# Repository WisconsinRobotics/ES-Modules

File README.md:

# ES-Modules
Daughter board code and CAD files for the 2018 rover

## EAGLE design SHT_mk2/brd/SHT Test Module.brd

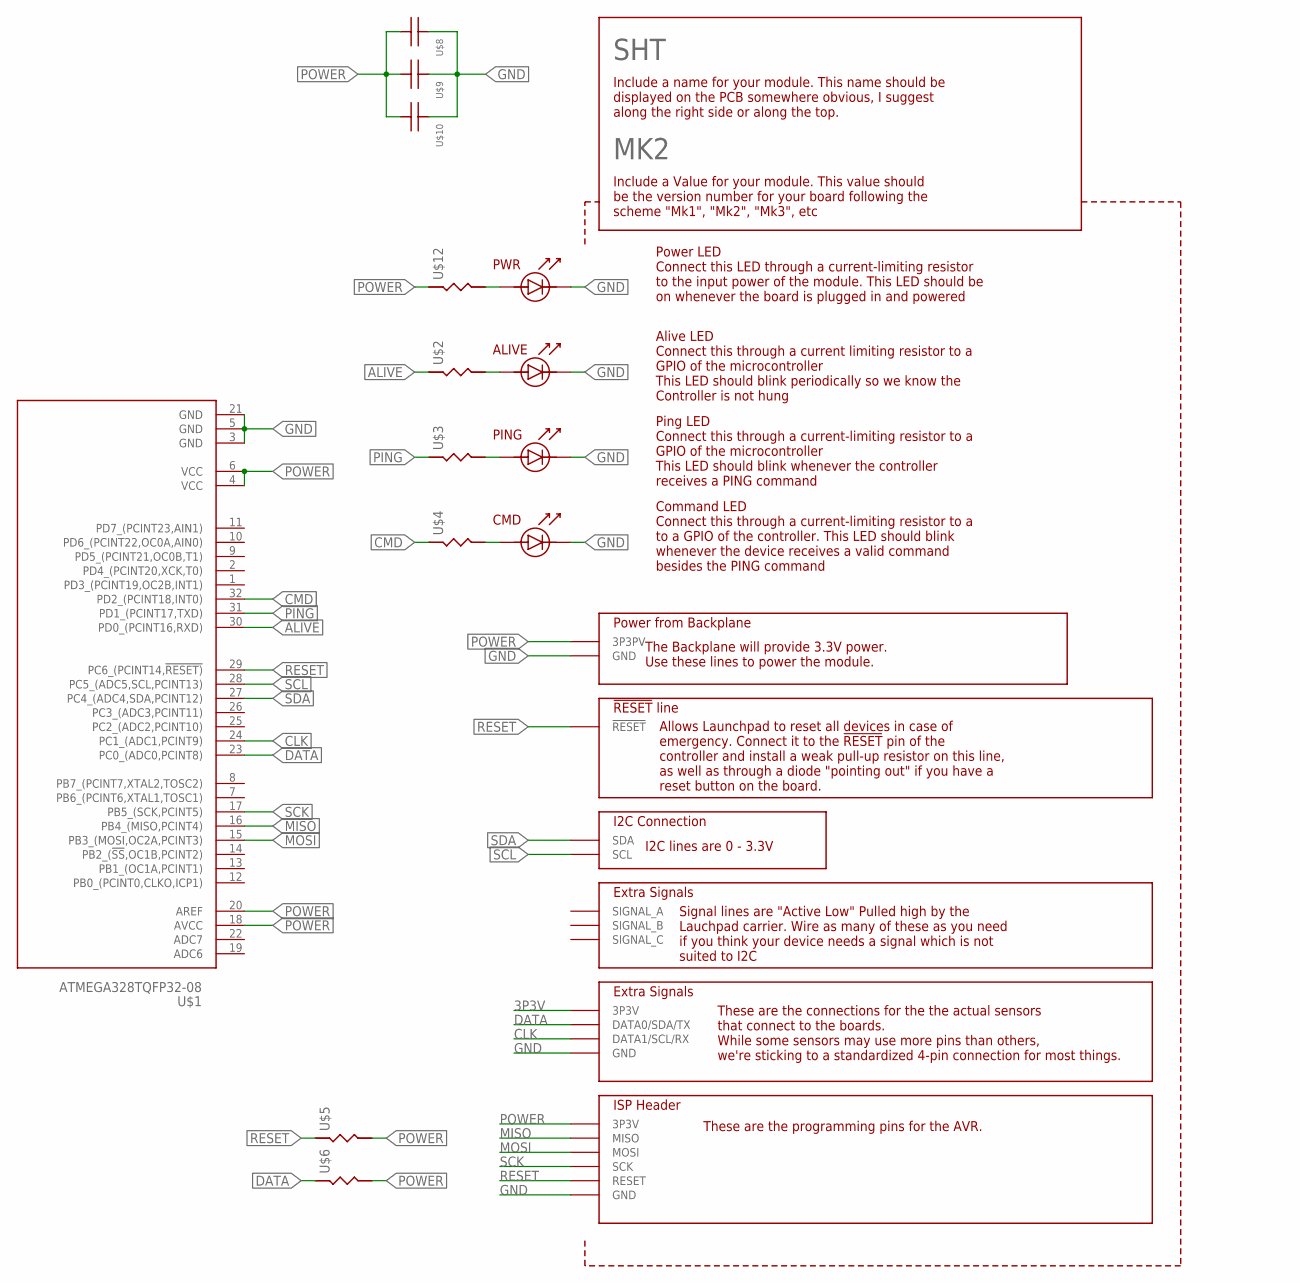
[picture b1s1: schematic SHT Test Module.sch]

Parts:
SHT: MK2; SENSOR_MODULE_MK1
U$1: ATMEGA328TQFP32-08; TQFP32-08
U$2, U$3, U$4, U$5, U$6, U$12: RESISTOR; 0805_STACKPOLERESISTOR
U$8, U$9, U$10: CAPACITOR-UNPOLARIZED0805; 0805_STACKPOLERESISTOR

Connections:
3P3V: SHT.3P3V@2 (3P3V), SHT.3P3V@3 (3P3V)
ALIVE: U$1.30 (PD0_(PCINT16,RXD)), U$2.P$1
CLK: SHT.DATA1@1 (DATA1/SCL/RX), SHT.DATA1@2 (DATA1/SCL/RX), U$1.24 (PC1_(ADC1,PCINT9))
CMD: U$1.32 (PD2_(PCINT18,INT0)), U$4.P$1
DATA: SHT.DATA0@1 (DATA0/SDA/TX), SHT.DATA0@2 (DATA0/SDA/TX), U$1.23 (PC0_(ADC0,PCINT8)), U$6.P$1
GND: SHT.ALIVELED_CATHODE, SHT.CMDLED_CATHODE, SHT.GND@1 (GND), SHT.GND@2 (GND), SHT.GND@3 (GND), SHT.GND@4 (GND), SHT.PINGLED_CATHODE, SHT.PWRLED_CATHODE, U$1.3 (GND), U$1.5 (GND), U$1.21 (GND), U$8.P$1, U$9.P$1, U$10.P$1
MISO: SHT.MISO, U$1.16 (PB4_(MISO,PCINT4))
MOSI: SHT.MOSI, U$1.15 (PB3_(MOSI,OC2A,PCINT3))
unnamed: SHT.PWRLED_ANODE, U$12.P$2
unnamed: SHT.ALIVELED_ANODE, U$2.P$2
unnamed: SHT.PINGLED_ANODE, U$3.P$2
unnamed: SHT.CMDLED_ANODE, U$4.P$2
PING: U$1.31 (PD1_(PCINT17,TXD)), U$3.P$1
POWER: SHT.3P3V@1 (3P3PV), SHT.3P3V@4 (3P3V), U$1.4 (VCC), U$1.6 (VCC), U$1.18 (AVCC), U$1.20 (AREF), U$5.P$2, U$6.P$2, U$8.P$2, U$9.P$2, U$10.P$2, U$12.P$1
RESET: SHT.RESET@1 (!RESET), SHT.RESET@2 (RESET), U$1.29 (PC6_(PCINT14,!RESET)), U$5.P$1
SCK: SHT.SCK, U$1.17 (PB5_(SCK,PCINT5))
SCL: SHT.SCL, U$1.28 (PC5_(ADC5,SCL,PCINT13))
SDA: SHT.SDA, U$1.27 (PC4_(ADC4,SDA,PCINT12))

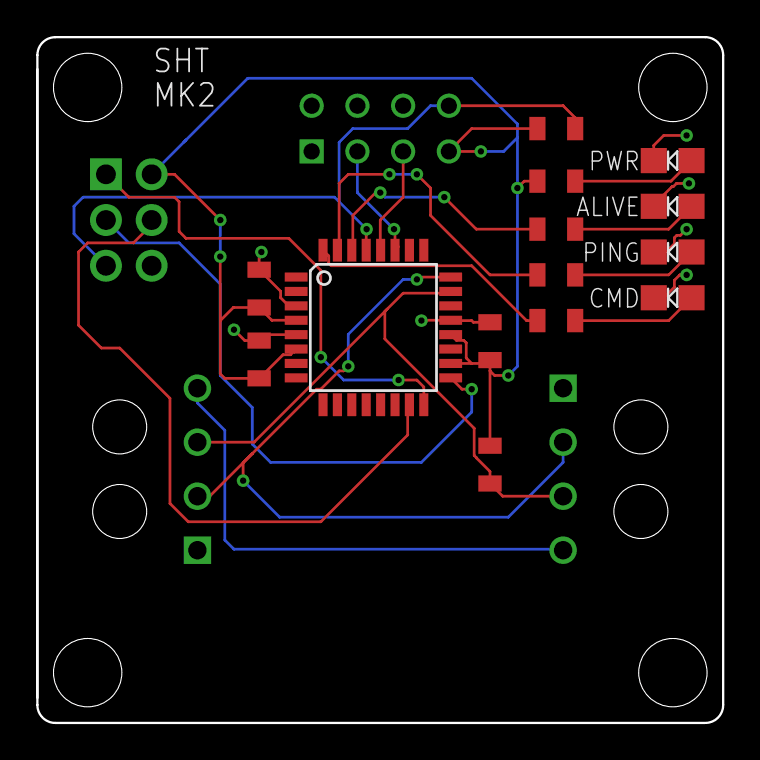
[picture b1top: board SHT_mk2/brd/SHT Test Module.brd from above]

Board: 2 copper layers, 38.1 x 38.1 mm, 11 parts (0 on the bottom side), 18 nets.

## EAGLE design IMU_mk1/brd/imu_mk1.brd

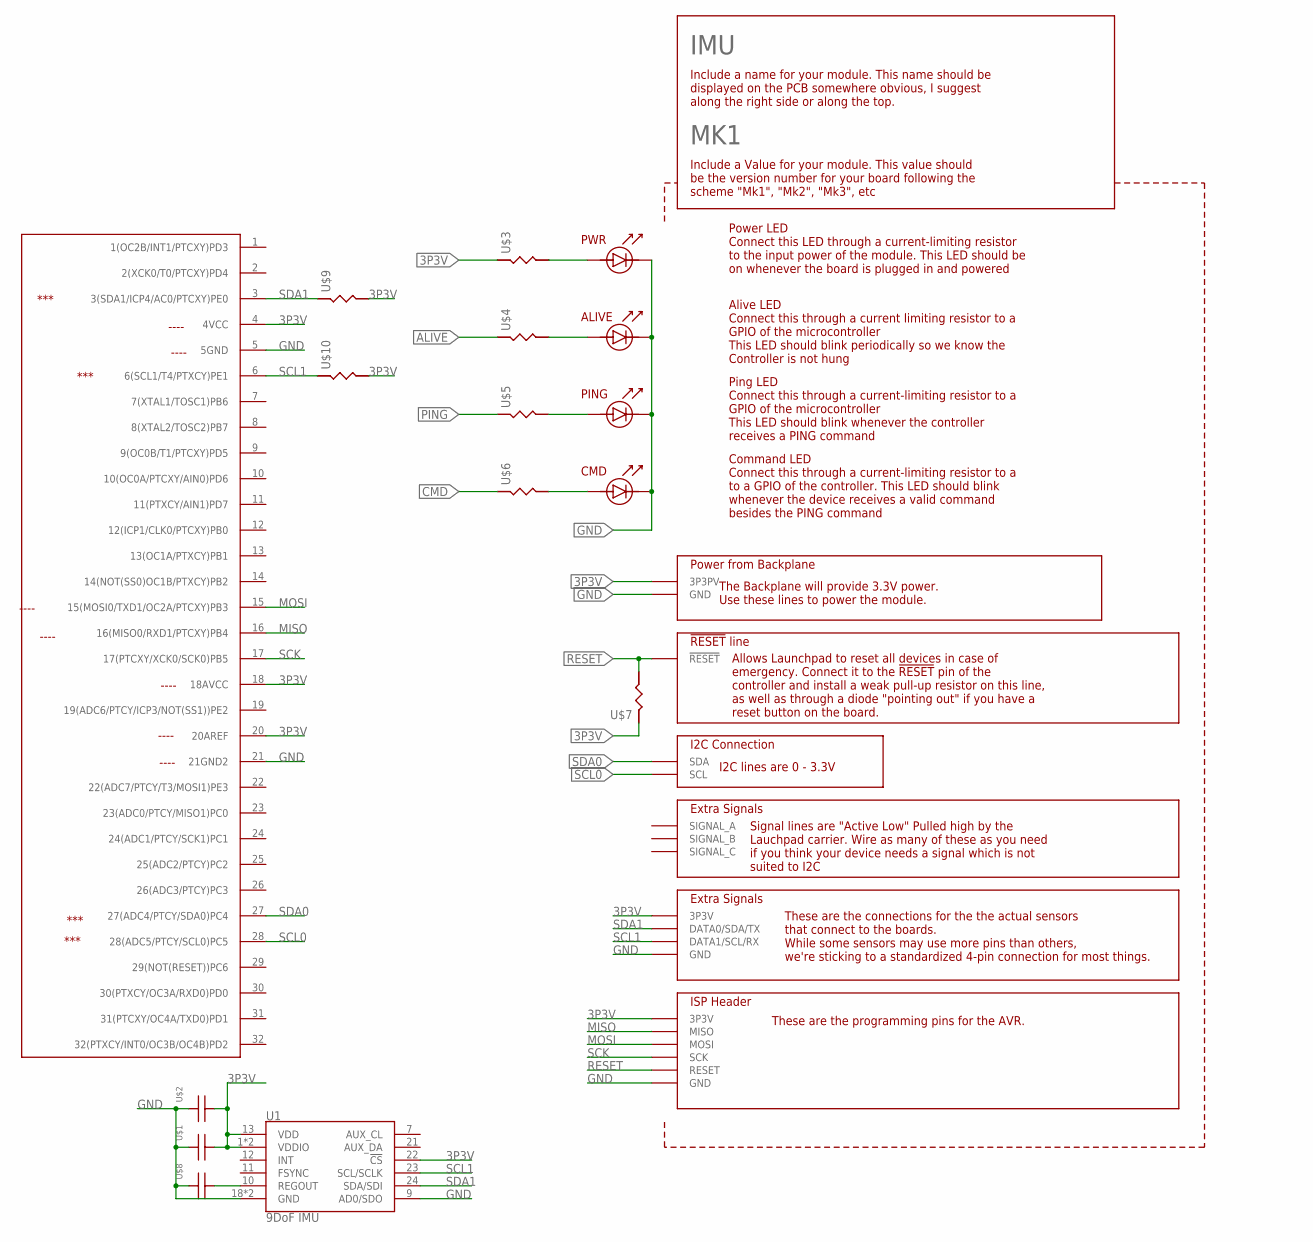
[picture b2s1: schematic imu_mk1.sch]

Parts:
IMU: MK1; SENSOR_MODULE_MK1
U1: 9DoF IMU; QFN24-3X3
U100: ATMEGA328PB; TQFP32-08
U$1, U$2, U$8: CAPACITOR-UNPOLARIZED0805; 0805_STACKPOLERESISTOR
U$3, U$4, U$5, U$6, U$7, U$9, U$10: RESISTOR; 0805_STACKPOLERESISTOR

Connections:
3P3V: IMU.3P3V@1 (3P3PV), IMU.3P3V@2 (3P3V), IMU.3P3V@3 (3P3V), IMU.3P3V@4 (3P3V), U1.1 (VDDIO), U1.8 (VDDIO), U1.13 (VDD), U1.22 (!CS), U100.4 (4VCC), U100.18 (18AVCC), U100.20 (20AREF), U$1.P$2, U$2.P$2, U$3.P$1, U$7.P$1, U$9.P$2, U$10.P$2
ALIVE: U$4.P$1
CMD: U$6.P$1
GND: IMU.ALIVELED_CATHODE, IMU.CMDLED_CATHODE, IMU.GND@1 (GND), IMU.GND@2 (GND), IMU.GND@3 (GND), IMU.GND@4 (GND), IMU.PINGLED_CATHODE, IMU.PWRLED_CATHODE, U1.9 (AD0/SDO), U1.18 (GND), U1.20 (GND), U100.5 (5GND), U100.21 (21GND2), U$1.P$1, U$2.P$1, U$8.P$1
MISO: IMU.MISO, U100.16 (16(MISO0/RXD1/PTCXY)PB4)
MOSI: IMU.MOSI, U100.15 (15(MOSI0/TXD1/OC2A/PTCXY)PB3)
unnamed: IMU.PWRLED_ANODE, U$3.P$2
unnamed: IMU.ALIVELED_ANODE, U$4.P$2
unnamed: IMU.PINGLED_ANODE, U$5.P$2
unnamed: IMU.CMDLED_ANODE, U$6.P$2
PING: U$5.P$1
REGOUT: U1.10 (REGOUT), U$8.P$2
RESET: IMU.RESET@1 (!RESET), IMU.RESET@2 (RESET), U$7.P$2
SCK: IMU.SCK, U100.17 (17(PTCXY/XCK0/SCK0)PB5)
SCL0: IMU.SCL, U100.28 (28(ADC5/PTCY/SCL0)PC5)
SCL1: IMU.DATA1@1 (DATA1/SCL/RX), IMU.DATA1@2 (DATA1/SCL/RX), U1.23 (SCL/SCLK), U100.6 (6(SCL1/T4/PTXCY)PE1), U$10.P$1
SDA0: IMU.SDA, U100.27 (27(ADC4/PTCY/SDA0)PC4)
SDA1: IMU.DATA0@1 (DATA0/SDA/TX), IMU.DATA0@2 (DATA0/SDA/TX), U1.24 (SDA/SDI), U100.3 (3(SDA1/ICP4/AC0/PTCXY)PE0), U$9.P$1

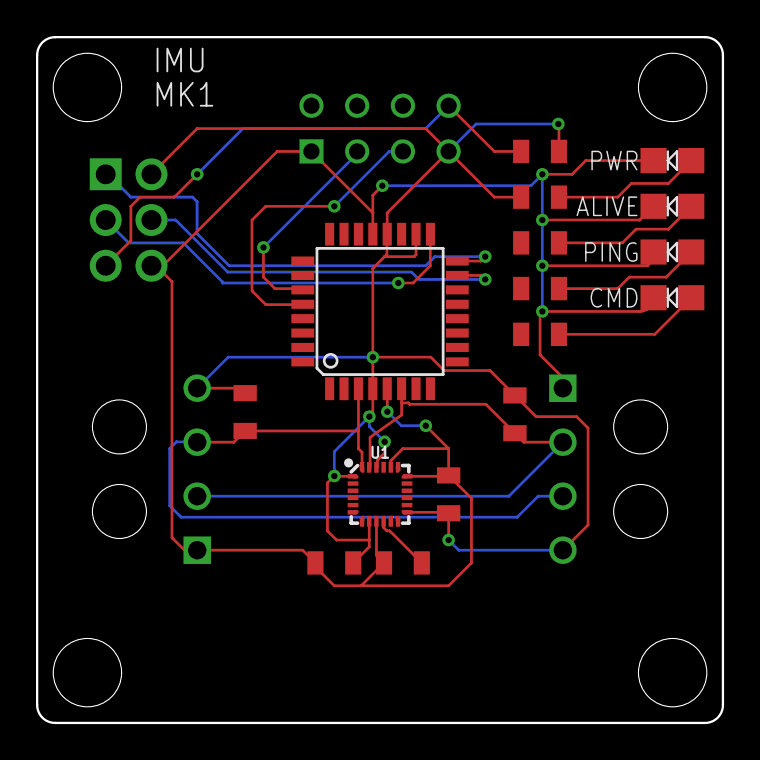
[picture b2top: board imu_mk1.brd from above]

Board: 2 copper layers, 38.1 x 38.1 mm, 13 parts (0 on the bottom side), 15 nets.

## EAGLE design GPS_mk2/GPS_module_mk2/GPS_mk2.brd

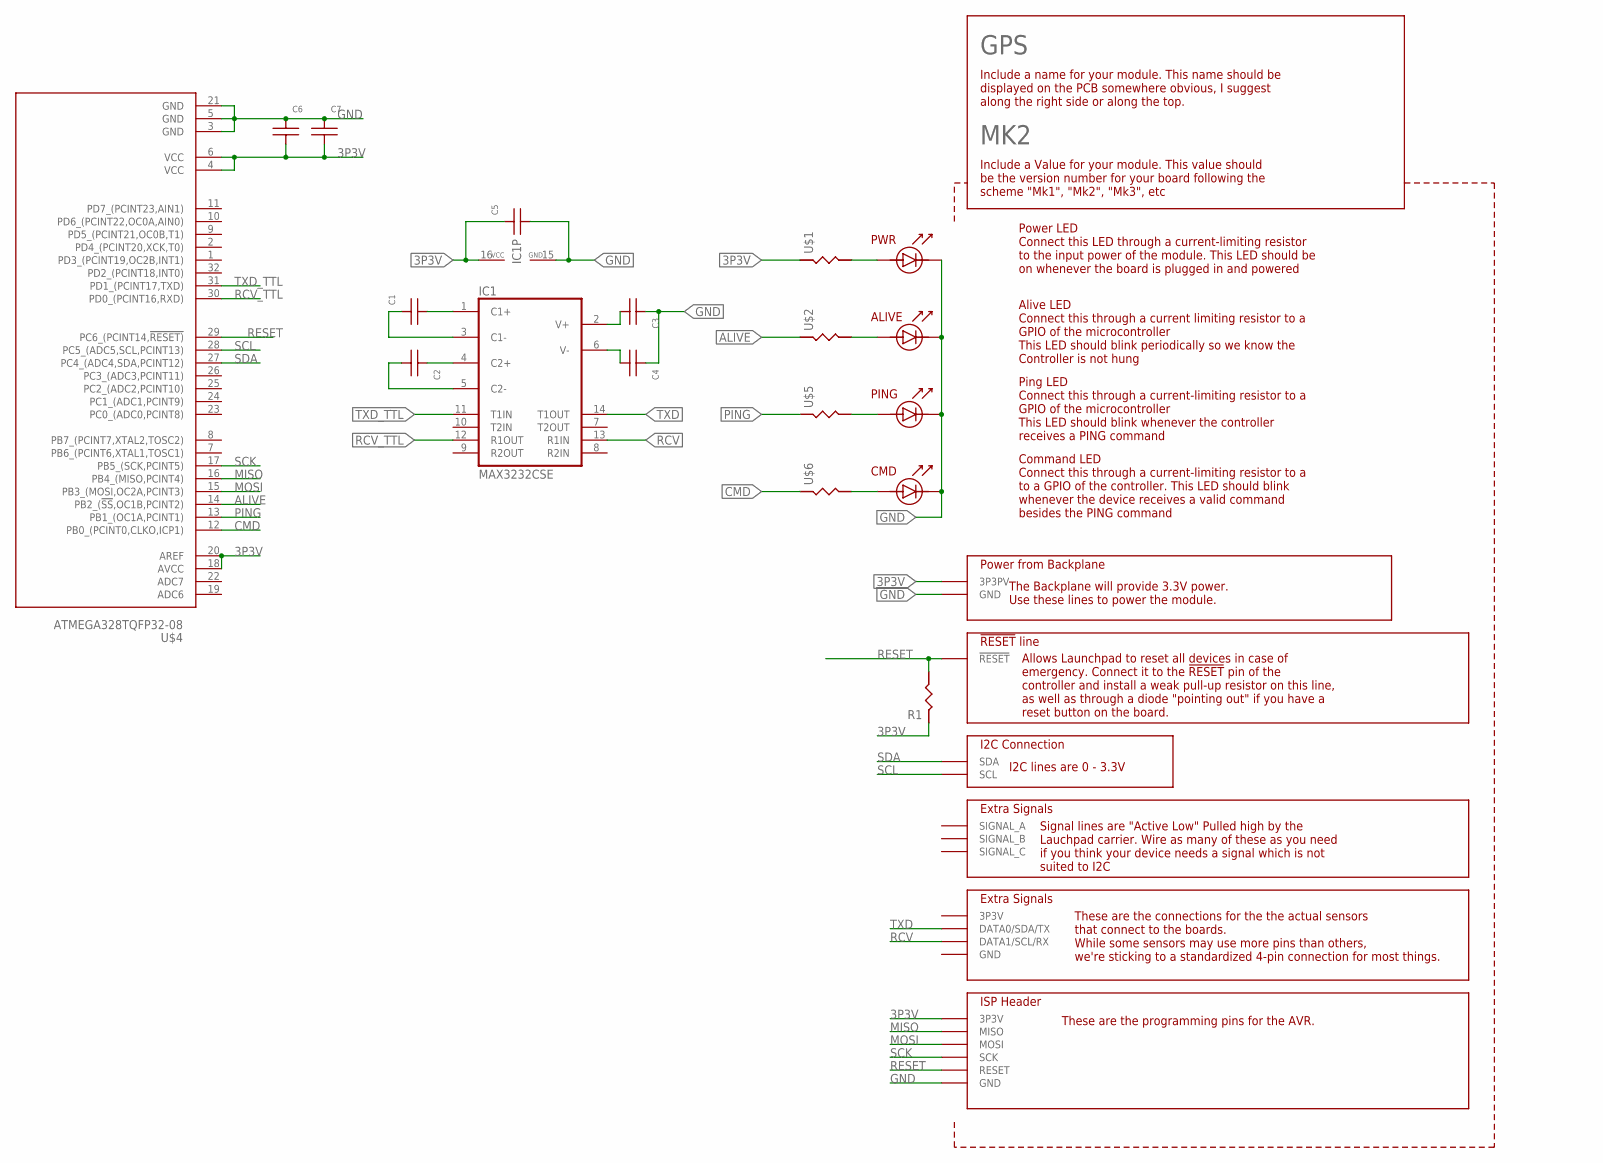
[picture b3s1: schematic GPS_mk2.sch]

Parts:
C1, C2, C3, C4, C5, C6, C7: CAPACITOR-UNPOLARIZED0805; 0805_STACKPOLERESISTOR
GPS: MK2; SENSOR_MODULE_MK1
IC1: MAX3232CSE; SO16
R1: RESISTOR; 0805_STACKPOLERESISTOR
U$1, U$2, U$5, U$6: RESISTOR; 0805_STACKPOLERESISTOR
U$4: ATMEGA328TQFP32-08; TQFP32-08

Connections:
3P3V: C5.P$1, C6.P$2, C7.P$2, GPS.3P3V@1 (3P3PV), GPS.3P3V@4 (3P3V), IC1.16 (VCC), R1.P$1, U$1.P$1, U$4.4 (VCC), U$4.6 (VCC), U$4.18 (AVCC), U$4.20 (AREF)
ALIVE: U$2.P$1, U$4.14 (PB2_(!SS,OC1B,PCINT2))
CMD: U$4.12 (PB0_(PCINT0,CLKO,ICP1)), U$6.P$1
GND: C3.P$1, C4.P$1, C5.P$2, C6.P$1, C7.P$1, GPS.ALIVELED_CATHODE, GPS.CMDLED_CATHODE, GPS.GND@1 (GND), GPS.GND@4 (GND), GPS.PINGLED_CATHODE, GPS.PWRLED_CATHODE, IC1.15 (GND), U$4.3 (GND), U$4.5 (GND), U$4.21 (GND)
MISO: GPS.MISO, U$4.16 (PB4_(MISO,PCINT4))
MOSI: GPS.MOSI, U$4.15 (PB3_(MOSI,OC2A,PCINT3))
unnamed: C1.P$2, IC1.1 (C1+)
unnamed: C2.P$1, IC1.4 (C2+)
unnamed: C1.P$1, IC1.3 (C1-)
unnamed: C2.P$2, IC1.5 (C2-)
unnamed: C4.P$2, IC1.6 (V-)
unnamed: GPS.ALIVELED_ANODE, U$2.P$2
unnamed: GPS.PWRLED_ANODE, U$1.P$2
unnamed: GPS.PINGLED_ANODE, U$5.P$2
unnamed: GPS.CMDLED_ANODE, U$6.P$2
unnamed: C3.P$2, IC1.2 (V+)
PING: U$4.13 (PB1_(OC1A,PCINT1)), U$5.P$1
RCV: GPS.DATA1@1 (DATA1/SCL/RX), GPS.DATA1@2 (DATA1/SCL/RX), IC1.13 (R1IN)
RCV_TTL: IC1.12 (R1OUT), U$4.30 (PD0_(PCINT16,RXD))
RESET: GPS.RESET@1 (!RESET), GPS.RESET@2 (RESET), R1.P$2, U$4.29 (PC6_(PCINT14,!RESET))
SCK: GPS.SCK, U$4.17 (PB5_(SCK,PCINT5))
SCL: GPS.SCL, U$4.28 (PC5_(ADC5,SCL,PCINT13))
SDA: GPS.SDA, U$4.27 (PC4_(ADC4,SDA,PCINT12))
TXD: GPS.DATA0@1 (DATA0/SDA/TX), GPS.DATA0@2 (DATA0/SDA/TX), IC1.14 (T1OUT)
TXD_TTL: IC1.11 (T1IN), U$4.31 (PD1_(PCINT17,TXD))

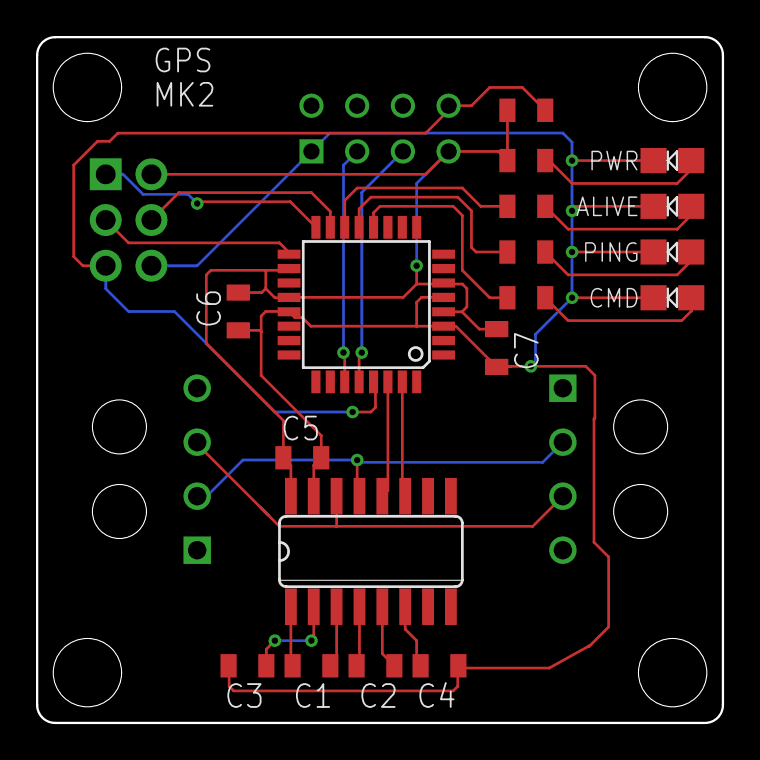
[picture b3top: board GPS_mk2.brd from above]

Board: 2 copper layers, 38.1 x 38.1 mm, 15 parts (0 on the bottom side), 25 nets.

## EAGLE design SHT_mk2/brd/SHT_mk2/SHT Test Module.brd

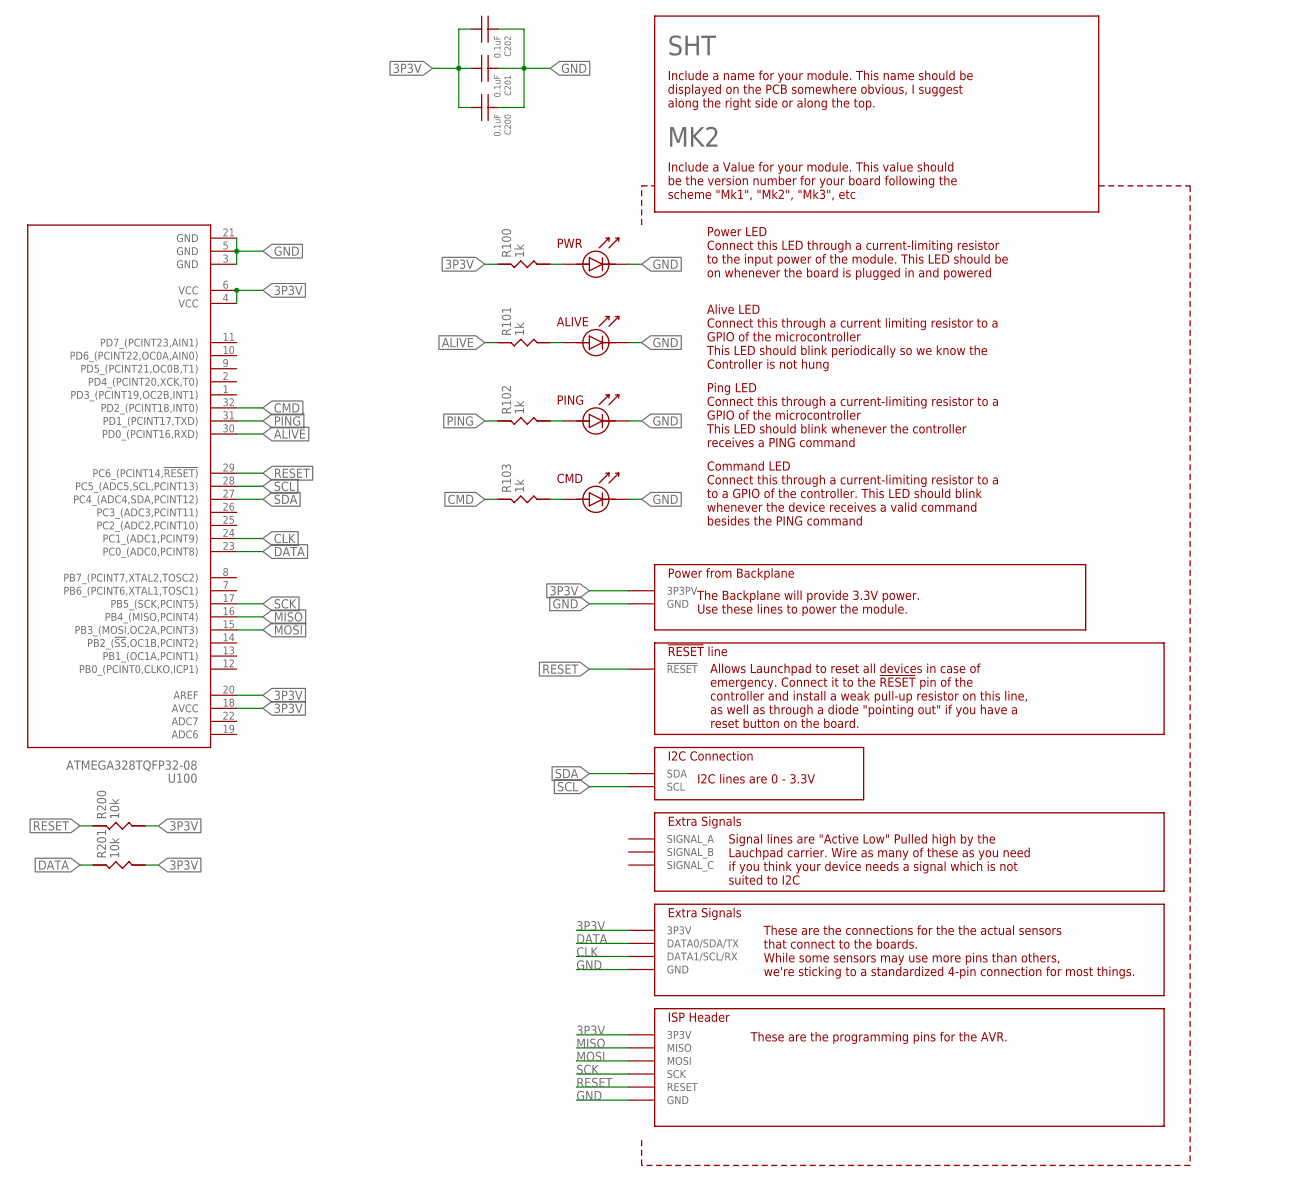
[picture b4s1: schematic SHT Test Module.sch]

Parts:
C200, C201, C202: 0.1uF; 0805_STACKPOLERESISTOR
R100, R101, R102, R103: 1k; 0805_STACKPOLERESISTOR
R200, R201: 10k; 0805_STACKPOLERESISTOR
SHT: MK2; SENSOR_MODULE_MK1
U100: ATMEGA328TQFP32-08; TQFP32-08

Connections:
3P3V: C200.P$2, C201.P$2, C202.P$2, R100.P$1, R200.P$2, R201.P$2, SHT.3P3V@1 (3P3PV), SHT.3P3V@2 (3P3V), SHT.3P3V@3 (3P3V), SHT.3P3V@4 (3P3V), U100.4 (VCC), U100.6 (VCC), U100.18 (AVCC), U100.20 (AREF)
ALIVE: R101.P$1, U100.30 (PD0_(PCINT16,RXD))
CLK: SHT.DATA1@1 (DATA1/SCL/RX), SHT.DATA1@2 (DATA1/SCL/RX), U100.24 (PC1_(ADC1,PCINT9))
CMD: R103.P$1, U100.32 (PD2_(PCINT18,INT0))
DATA: R201.P$1, SHT.DATA0@1 (DATA0/SDA/TX), SHT.DATA0@2 (DATA0/SDA/TX), U100.23 (PC0_(ADC0,PCINT8))
GND: C200.P$1, C201.P$1, C202.P$1, SHT.ALIVELED_CATHODE, SHT.CMDLED_CATHODE, SHT.GND@1 (GND), SHT.GND@2 (GND), SHT.GND@3 (GND), SHT.GND@4 (GND), SHT.PINGLED_CATHODE, SHT.PWRLED_CATHODE, U100.3 (GND), U100.5 (GND), U100.21 (GND)
MISO: SHT.MISO, U100.16 (PB4_(MISO,PCINT4))
MOSI: SHT.MOSI, U100.15 (PB3_(MOSI,OC2A,PCINT3))
unnamed: R100.P$2, SHT.PWRLED_ANODE
unnamed: R101.P$2, SHT.ALIVELED_ANODE
unnamed: R102.P$2, SHT.PINGLED_ANODE
unnamed: R103.P$2, SHT.CMDLED_ANODE
PING: R102.P$1, U100.31 (PD1_(PCINT17,TXD))
RESET: R200.P$1, SHT.RESET@1 (!RESET), SHT.RESET@2 (RESET), U100.29 (PC6_(PCINT14,!RESET))
SCK: SHT.SCK, U100.17 (PB5_(SCK,PCINT5))
SCL: SHT.SCL, U100.28 (PC5_(ADC5,SCL,PCINT13))
SDA: SHT.SDA, U100.27 (PC4_(ADC4,SDA,PCINT12))

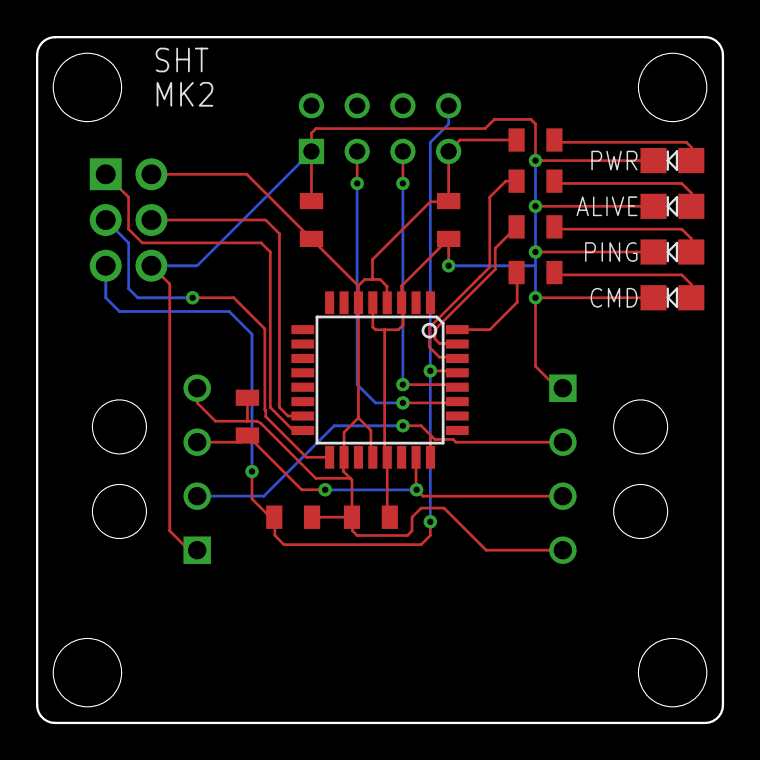
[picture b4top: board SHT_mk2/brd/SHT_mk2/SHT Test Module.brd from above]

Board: 2 copper layers, 38.1 x 38.1 mm, 11 parts (0 on the bottom side), 17 nets.

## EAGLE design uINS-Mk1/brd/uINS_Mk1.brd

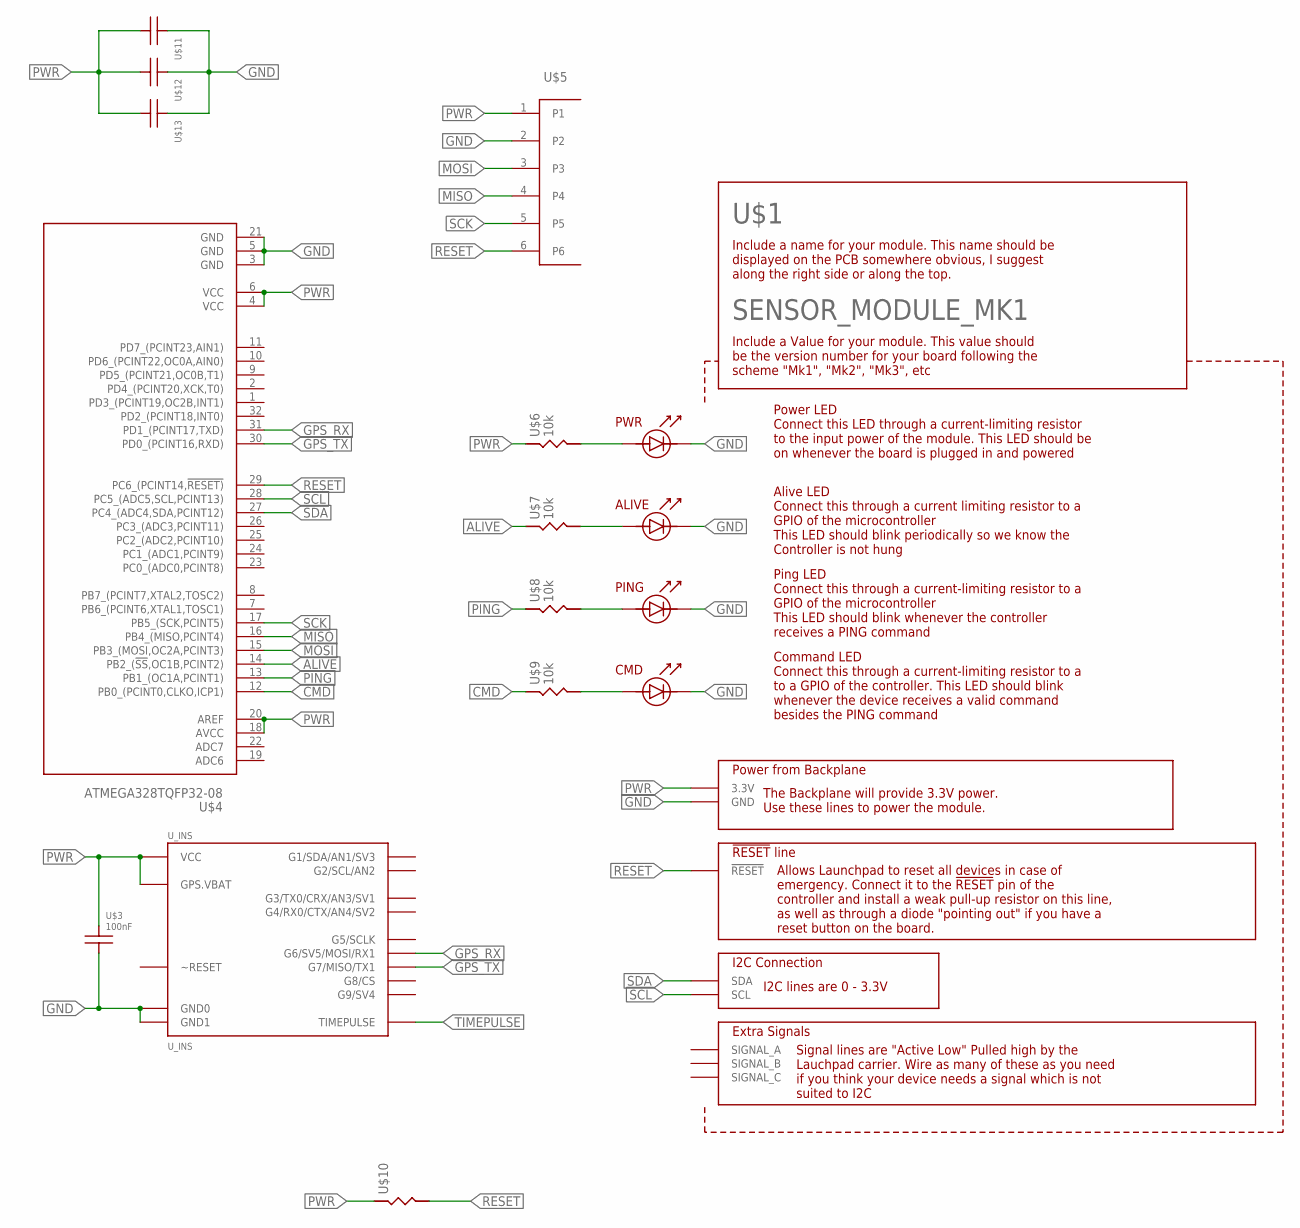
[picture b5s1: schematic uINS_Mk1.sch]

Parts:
U$1: SENSOR_MODULE_MK1
U$3: 100nF; 0805_STACKPOLERESISTOR
U$4: ATMEGA328TQFP32-08; TQFP32-08
U$5: 6PIN-HEADER2X3; 6PINHEADER_CORRECT
U$6, U$7, U$8, U$9: 10k; 0805_STACKPOLERESISTOR
U$10: RESISTOR; 0805_STACKPOLERESISTOR
U$11, U$12, U$13: CAPACITOR-UNPOLARIZED0805; 0805_STACKPOLERESISTOR
U_INS: U_INS

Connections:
ALIVE: U$4.14 (PB2_(!SS,OC1B,PCINT2)), U$7.P$1
CMD: U$4.12 (PB0_(PCINT0,CLKO,ICP1)), U$9.P$1
GND: U$1.ALIVELED_CATHODE, U$1.CMDLED_CATHODE, U$1.GND, U$1.PINGLED_CATHODE, U$1.PWRLED_CATHODE, U$3.P$2, U$4.3 (GND), U$4.5 (GND), U$4.21 (GND), U$5.2, U$11.P$1, U$12.P$1, U$13.P$1, U_INS.GND0, U_INS.GND1
GPS_RX: U$4.31 (PD1_(PCINT17,TXD)), U_INS.G6/RX1/MOSI (G6/SV5/MOSI/RX1)
GPS_TX: U$4.30 (PD0_(PCINT16,RXD)), U_INS.G7/TX1/MISO (G7/MISO/TX1)
MISO: U$4.16 (PB4_(MISO,PCINT4)), U$5.4
MOSI: U$4.15 (PB3_(MOSI,OC2A,PCINT3)), U$5.3
unnamed: U$1.PWRLED_ANODE, U$6.P$2
unnamed: U$1.ALIVELED_ANODE, U$7.P$2
unnamed: U$1.PINGLED_ANODE, U$8.P$2
unnamed: U$1.CMDLED_ANODE, U$9.P$2
PING: U$4.13 (PB1_(OC1A,PCINT1)), U$8.P$1
PWR: U$1.3P3V (3.3V), U$3.P$1, U$4.4 (VCC), U$4.6 (VCC), U$4.18 (AVCC), U$4.20 (AREF), U$5.1, U$6.P$1, U$10.P$1, U$11.P$2, U$12.P$2, U$13.P$2, U_INS.GPS.VBAT, U_INS.VCC
RESET: U$1.RESET (!RESET), U$4.29 (PC6_(PCINT14,!RESET)), U$5.6, U$10.P$2
SCK: U$4.17 (PB5_(SCK,PCINT5)), U$5.5
SCL: U$1.SCL, U$4.28 (PC5_(ADC5,SCL,PCINT13))
SDA: U$1.SDA, U$4.27 (PC4_(ADC4,SDA,PCINT12))
TIMEPULSE: U_INS.GPS.TIMEPULSE (TIMEPULSE)

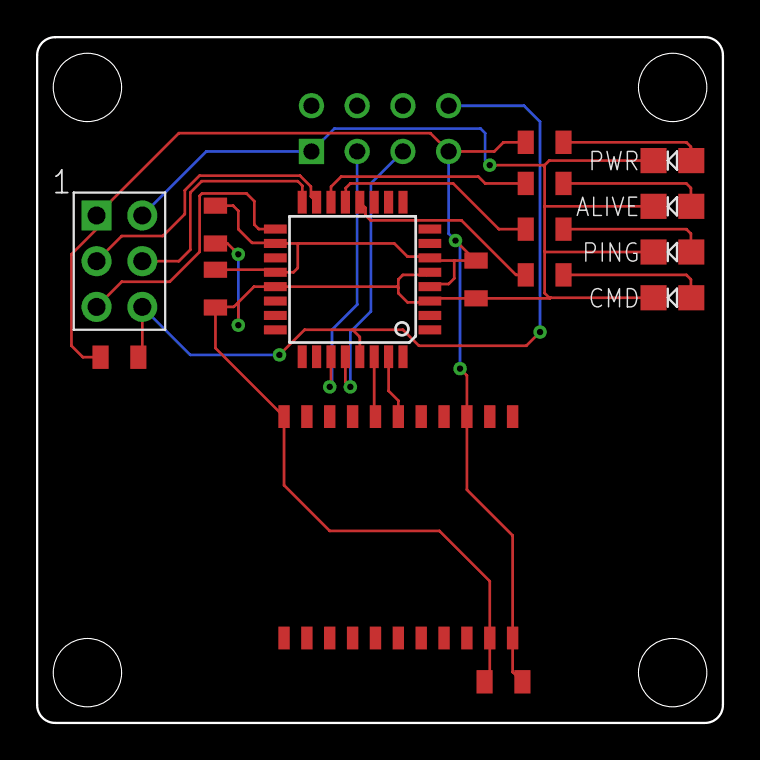
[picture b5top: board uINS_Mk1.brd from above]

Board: 2 copper layers, 38.1 x 38.1 mm, 13 parts (0 on the bottom side), 17 nets.

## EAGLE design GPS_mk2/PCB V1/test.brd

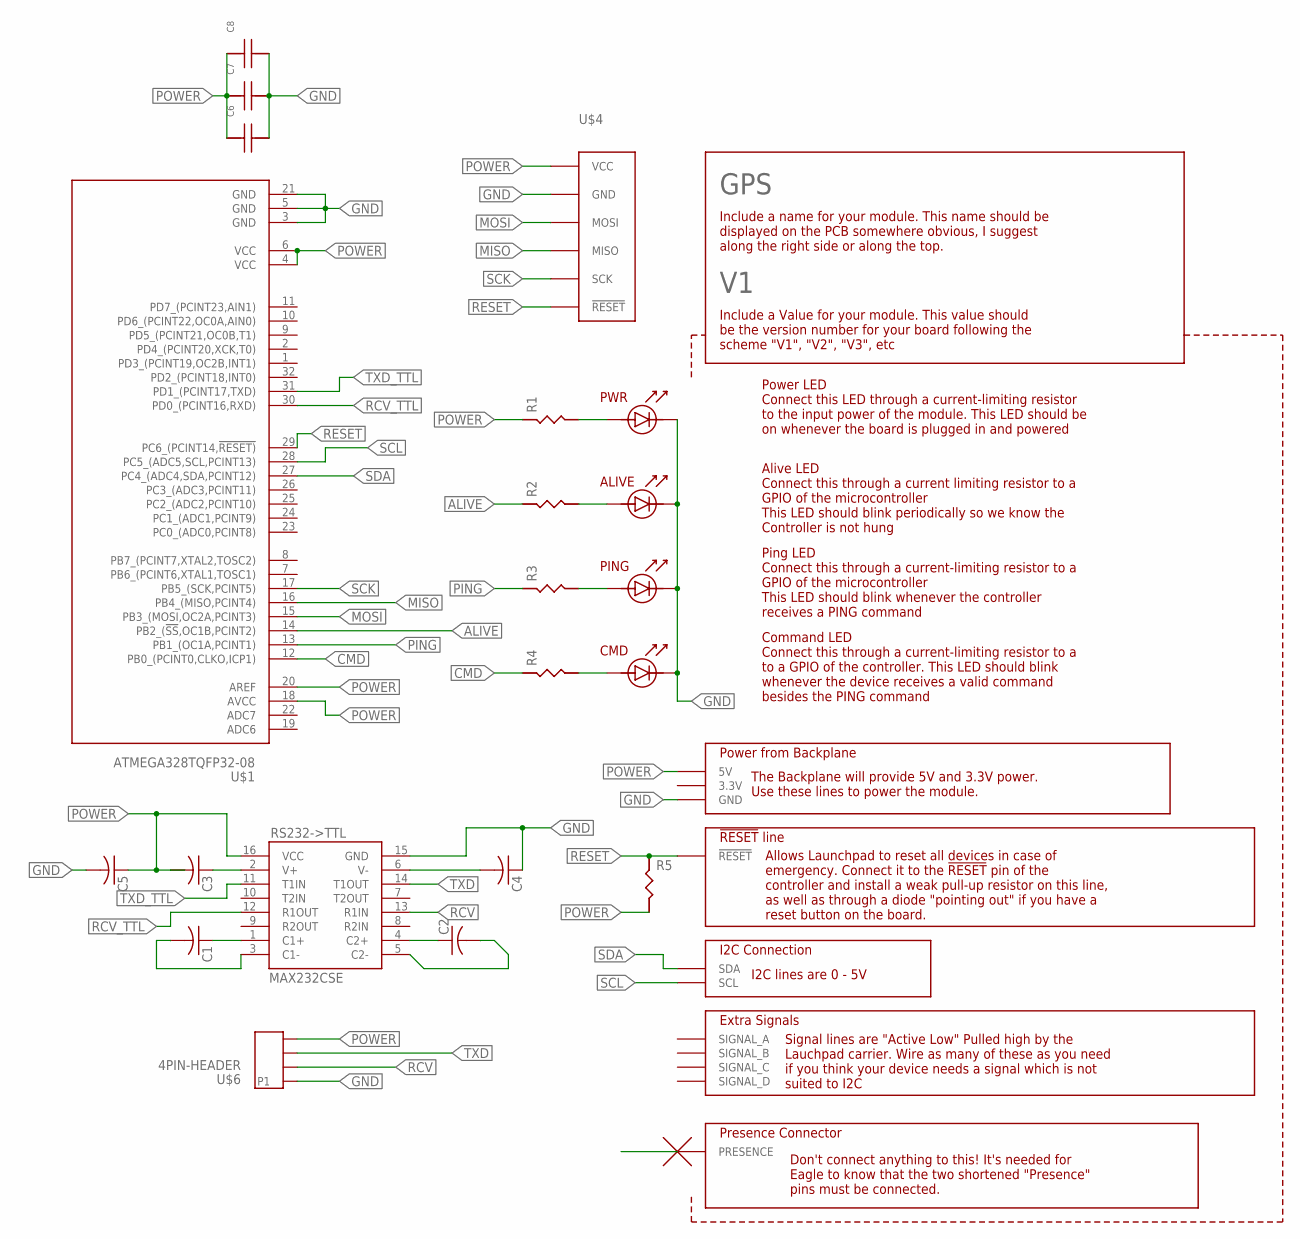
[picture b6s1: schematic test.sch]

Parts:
C1, C2, C3, C4, C5: C-USC0805; C0805
C6, C7, C8: CAPACITOR-UNPOLARIZED0805; 0805_STACKPOLERESISTOR
GPS: V1; SUBSYSTEM2016_V2-SMALL
R1, R2, R3, R4, R5: RESISTOR; 0805_STACKPOLERESISTOR
RS232->TTL: MAX232CSE
U$1: ATMEGA328TQFP32-08; TQFP32-08
U$4: ISP_PROGRAMMING_HEADER; 6PINHEADER_CORRECT
U$6: 4PIN-HEADER; 4HEADER_10MIL

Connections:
ALIVE: R2.P$1, U$1.14 (PB2_(!SS,OC1B,PCINT2))
CMD: R4.P$1, U$1.12 (PB0_(PCINT0,CLKO,ICP1))
GND: C4.1, C5.2, C6.P$2, C7.P$2, C8.P$2, GPS.A7 (GND), GPS.A8 (GND), GPS.A9 (GND), GPS.A10 (GND), GPS.ALIVELED_CATHODE, GPS.CMDLED_CATHODE, GPS.PINGLED_CATHODE, GPS.PWRLED_CATHODE, RS232->TTL.15 (GND), U$1.3 (GND), U$1.5 (GND), U$1.21 (GND), U$4.6 (GND), U$6.P$1 (P1)
MISO: U$1.16 (PB4_(MISO,PCINT4)), U$4.1 (MISO)
MOSI: U$1.15 (PB3_(MOSI,OC2A,PCINT3)), U$4.4 (MOSI)
unnamed: GPS.A2 (PRESENCE), GPS.B17 (PRESENCE)
unnamed: C1.1, RS232->TTL.1 (C1+)
unnamed: C1.2, RS232->TTL.3 (C1-)
unnamed: C2.1, RS232->TTL.4 (C2+)
unnamed: C2.2, RS232->TTL.5 (C2-)
unnamed: C3.1, RS232->TTL.2 (V+)
unnamed: GPS.CMDLED_ANODE, R4.P$2
unnamed: GPS.PWRLED_ANODE, R1.P$2
unnamed: GPS.ALIVELED_ANODE, R2.P$2
unnamed: GPS.PINGLED_ANODE, R3.P$2
PING: R3.P$1, U$1.13 (PB1_(OC1A,PCINT1))
POWER: C3.2, C5.1, C6.P$1, C7.P$1, C8.P$1, GPS.B2 (5V), GPS.B3 (5V), R1.P$1, R5.P$2, RS232->TTL.16 (VCC), U$1.4 (VCC), U$1.6 (VCC), U$1.18 (AVCC), U$1.20 (AREF), U$4.2 (VCC), U$6.P$4
RCV: RS232->TTL.13 (R1IN), U$6.P$2
RCV_TTL: RS232->TTL.12 (R1OUT), U$1.30 (PD0_(PCINT16,RXD))
RESET: GPS.B5 (!RESET), GPS.B6 (!RESET), R5.P$1, U$1.29 (PC6_(PCINT14,!RESET)), U$4.5 (!RESET)
SCK: U$1.17 (PB5_(SCK,PCINT5)), U$4.3 (SCK)
SCL: GPS.B9 (SCL), GPS.B10 (SCL), U$1.28 (PC5_(ADC5,SCL,PCINT13))
SDA: GPS.B7 (SDA), GPS.B8 (SDA), U$1.27 (PC4_(ADC4,SDA,PCINT12))
TXD: RS232->TTL.14 (T1OUT), U$6.P$3
TXD_TTL: RS232->TTL.11 (T1IN), U$1.31 (PD1_(PCINT17,TXD))
V-: C4.2, RS232->TTL.6 (V-)

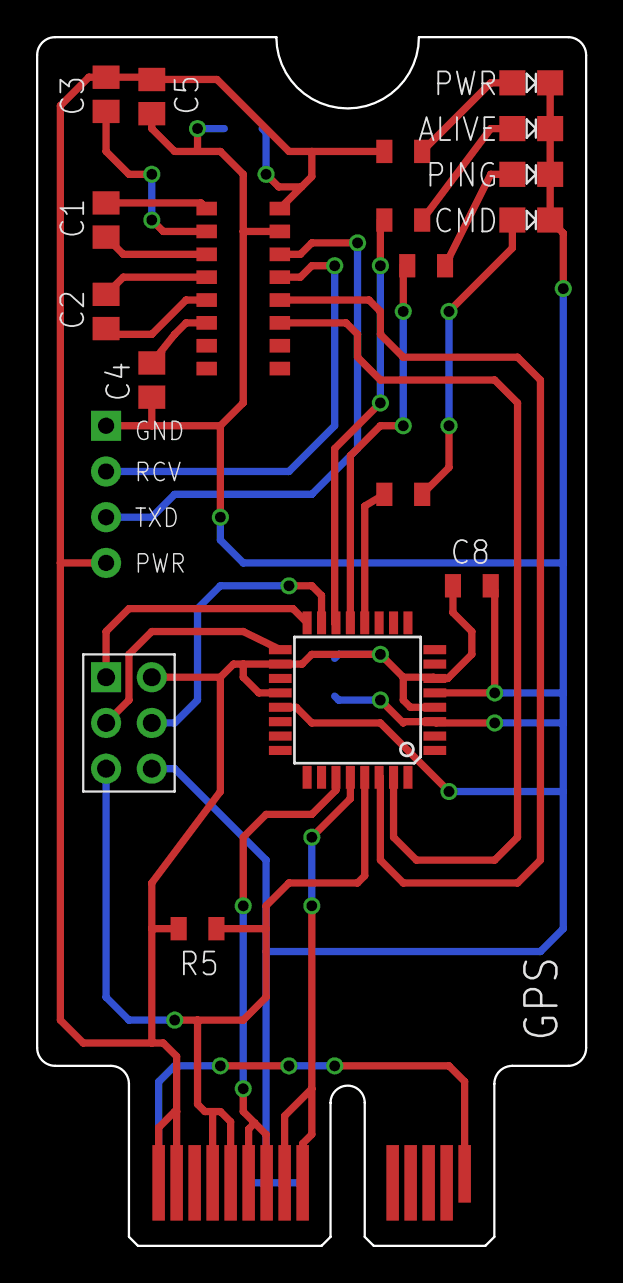
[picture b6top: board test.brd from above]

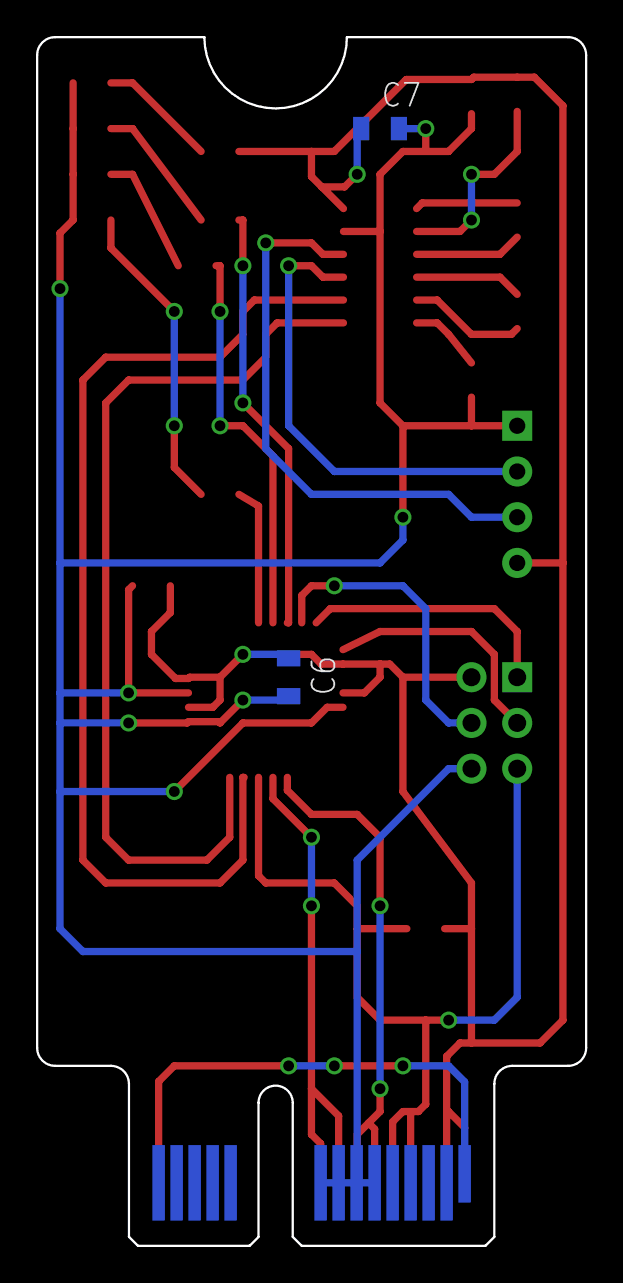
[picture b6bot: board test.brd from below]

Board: 2 copper layers, 30.5 x 67.2 mm, 18 parts (2 on the bottom side), 26 nets.

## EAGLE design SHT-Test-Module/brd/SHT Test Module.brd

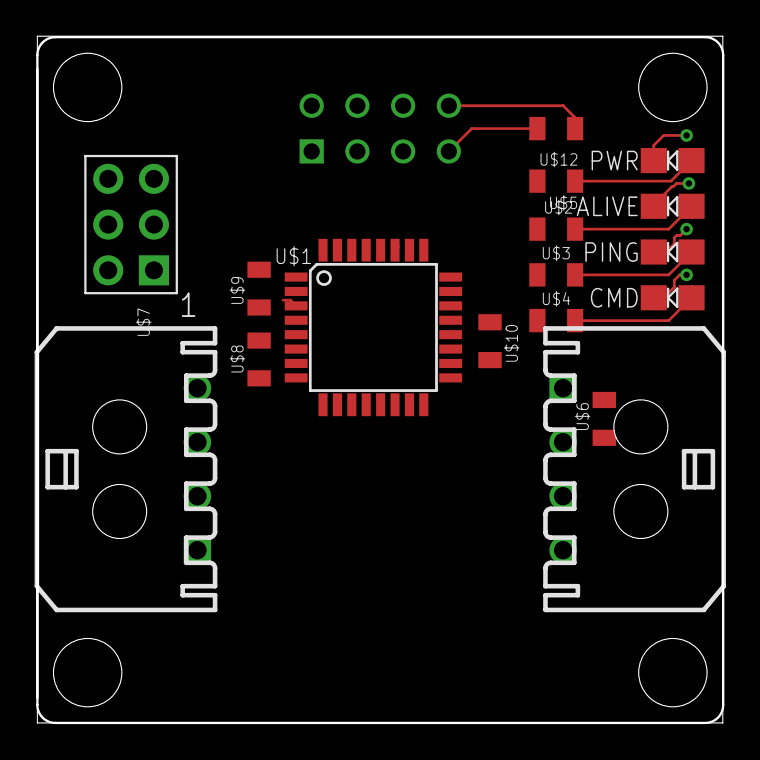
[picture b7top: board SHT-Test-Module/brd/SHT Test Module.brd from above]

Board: 2 copper layers, 38.1 x 38.1 mm, 12 parts (0 on the bottom side), 18 nets.

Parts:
TESTMOUDULE: SENSOR_MODULE_MK1
U$1: ATMEGA328TQFP32-08; TQFP32-08
U$2, U$3, U$4, U$5, U$6, U$8, U$9, U$10, U$12: 0805_STACKPOLERESISTOR
U$7: 6PINHEADER_CORRECT

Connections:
3P3V: TESTMOUDULE.3P3V@2, TESTMOUDULE.3P3V@3
ALIVE: U$1.30, U$2.P$1
CLK: TESTMOUDULE.DATA1@1, TESTMOUDULE.DATA1@2, U$1.24
CMD: U$1.32, U$4.P$1
DATA: TESTMOUDULE.DATA0@1, TESTMOUDULE.DATA0@2, U$1.23, U$6.P$1
GND: TESTMOUDULE.ALIVELED_CATHODE, TESTMOUDULE.CMDLED_CATHODE, TESTMOUDULE.GND@1, TESTMOUDULE.GND@2, TESTMOUDULE.GND@3, TESTMOUDULE.PINGLED_CATHODE, TESTMOUDULE.PWRLED_CATHODE, U$1.3, U$1.5, U$1.21, U$7.6, U$8.P$1, U$9.P$1, U$10.P$1
MISO: U$1.16, U$7.1
MOSI: U$1.15, U$7.4
unnamed: TESTMOUDULE.PWRLED_ANODE, U$12.P$2
unnamed: TESTMOUDULE.ALIVELED_ANODE, U$2.P$2
unnamed: TESTMOUDULE.PINGLED_ANODE, U$3.P$2
unnamed: TESTMOUDULE.CMDLED_ANODE, U$4.P$2
PING: U$1.31, U$3.P$1
POWER: TESTMOUDULE.3P3V@1, U$1.4, U$1.6, U$1.18, U$1.20, U$5.P$2, U$6.P$2, U$7.2, U$8.P$2, U$9.P$2, U$10.P$2, U$12.P$1
RESET: TESTMOUDULE.RESET, U$1.29, U$5.P$1, U$7.5
SCK: U$1.17, U$7.3
SCL: TESTMOUDULE.SCL, U$1.28
SDA: TESTMOUDULE.SDA, U$1.27

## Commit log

2017-07-25 initial commit with boards for a test SHT module, and a hypothetical uINS board. Also includes SHT code from the Ascent ES, as it should port without issue.
2017-07-25 placeholder in the src to appease github.
2017-08-14 Started revamping GPS code for last year's GPS. Moving ahead assuming we're using it for now
2017-09-26 updated library. Apparently I wrote code
2017-10-10 Added SHT board files
2017-10-10 testing change to i2c library
2017-10-11 some fixes for build issues in GPS code. Doesn't appear to work yet.
2017-10-17 updated board templates and modified existing boards to use the mk2 templates.
2017-10-24 bunch of stuff I forgot to commit
2017-10-26 IMU layout. GPS layout tweaks
2017-11-13 cleaning up some GPS code in preparation for new hardware.
2017-11-27 I don't know. I guess I did things.
2017-11-27 working on getting the SHT running
2017-11-29 stuff
2017-11-29 trying to fix SHT
2017-11-30 pulled over the SHT mk2 brd files from nathan's branch.
2018-01-10 deleted INS files
2018-05-04 complete restructure. Removed sch and brd files. Uploaded SHT and ride height src.
2018-05-05 refactor of ride height controller. Made the i2c queue atomic. Untested.
2018-05-08 fixed some annoying whitespace inconsistancy.
2018-05-09 added test case for returning data
2018-05-09 disabled interrupts during checkforpackets. Seems to work?
2018-05-09 Did some cleanup
2018-05-09 cleaned up the actuator selection process. Ready to test.
2018-05-10 Ride Height works!
2018-05-10 I2c stuff works too!
2018-05-10 Flipped the direction
2018-05-11 Some cleanup. Set the actuators to STOP_PWM on startup so we don't move.
2018-05-16 Fixed PWM output
2018-05-16 fixed PWM stuff and some control issues
2018-05-19 changed the payload structure to contain fields for both actuator directions.
2018-05-19 fixed ride height bug
2018-05-19 more rideheight fixes!
2018-05-19 ride_height_controller/ride_height.c
2018-05-19 fixed the ride height bugs and added correct files.

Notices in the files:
parts and their libraries:
SparkFun-Sensors: Licensing: Creative Commons ShareAlike 4.0 International - https://creativecommons.org/licenses/by-sa/4.0
